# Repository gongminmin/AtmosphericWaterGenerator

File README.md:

# Atmospheric Water Generator

Atmospheric water generator (AWG) is a device for extracting fresh water from air. There are 0.0001% of water exists in the atmosphere. Even the desert air is not completely dry. Extract it for using is better than nothing. If the extraction is carried out near the ocean, where the air humidity is extremely high, the amount of fresh water obtained can be considerable. 

This is a simple open-source AWG design, suitable for home use. We'd like to make it easy to implement, so people can build it at home. The goals are:

* Low building cost. Off-shelve parts as much as possible.
* Easy to duplicate.
* Low operating cost and low power.
* Simple structure and easy maintenance.
* Small size and light weight.
* Safe and reliable.

## Principle

To extract water from air, we need a cold source. It condenses the water out for us to collect. The dry and cold air then be used to cool down the heat from the cold source device.

## Design

We use a [Peltier cooling plate](https://en.wikipedia.org/wiki/Thermoelectric_cooling) as the cold source. It's a solid semiconductor device, no moving part, easy to use. It as a cold side and a hot side. Two water cooling loops are circuiting between the surfaces of cooling plate to radiators. One loop carries the heat from a radiator to the cold side, makes the radiator cold. The other loop carries the heat from hot side to a radiator, exhaust the heat. The condensed water generated from the cold radiator drops down, collected by a bottle. The cooling plate is power consuming. We need a circuit to control it, keeping the temperature of the cold radiator in a certain range.

Most of the components are off-shelve ones. They are mounted to a frame by 3D printed adapters.

## Directories

* 3DModel folder is the 3D model design of some components. It's in STL format, ready for 3D printing.
* Circuit folder is the electric design of the system. The files can be open by [KiCad](https://kicad-pcb.org/)
* Code folder is the Arduino code for the control module.
* Doc folder contains some documents

## License

This project is distributed under the terms of MIT License. See [LICENSE](LICENSE) for details.

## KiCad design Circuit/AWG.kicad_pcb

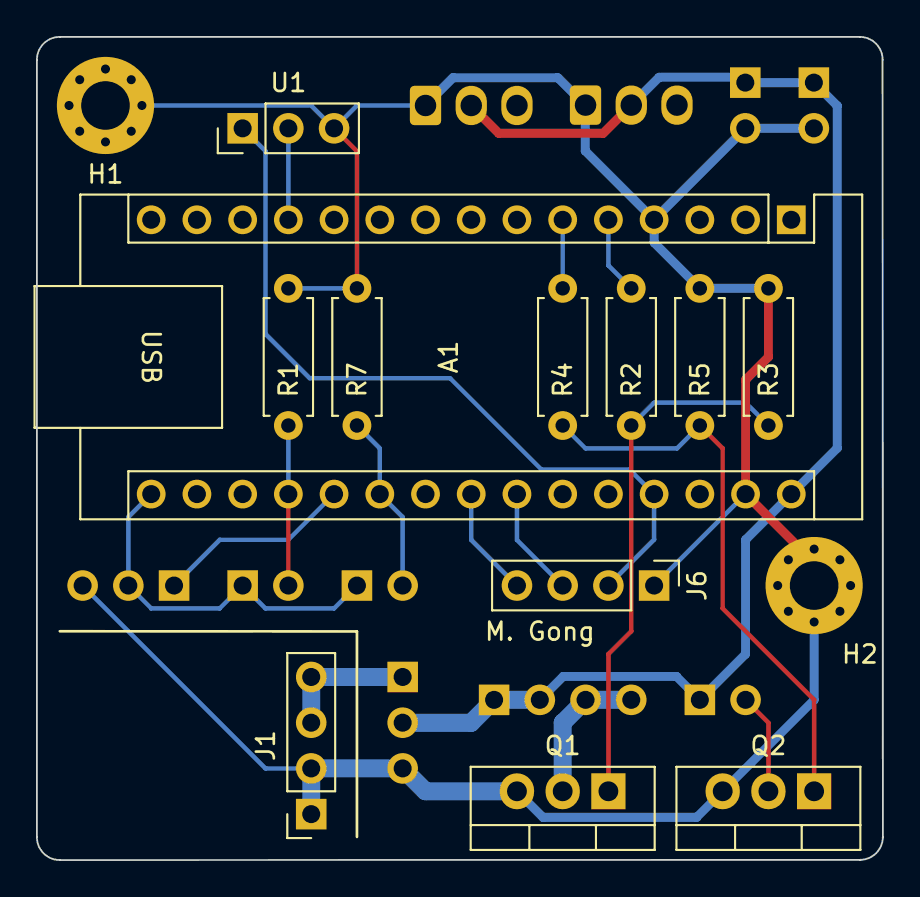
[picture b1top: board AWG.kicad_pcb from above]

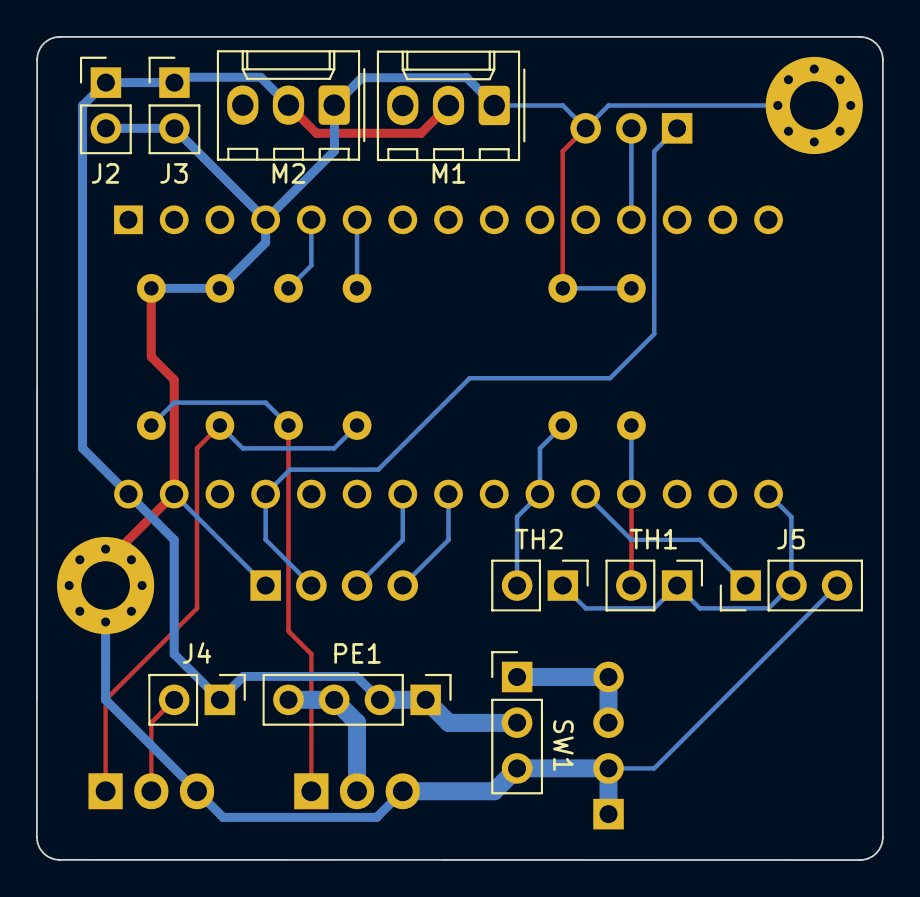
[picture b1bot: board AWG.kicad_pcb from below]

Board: 2 copper layers, 47.0 x 45.7 mm, 24 parts (10 on the bottom side), 17 nets.

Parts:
A1: Arduino_Nano_v3.x; Arduino_Nano
H1: H1; MountingHole_2.7mm_M2.5_Pad_Via
H2: H2; MountingHole_2.7mm_M2.5_Pad_Via
J1: Power; PinSocket_1x04_P2.54mm_Vertical
J2: Pump 1; PinHeader_1x02_P2.54mm_Vertical
J3: Pump 2; PinHeader_1x02_P2.54mm_Vertical
J4: Pump 3; PinHeader_1x02_P2.54mm_Vertical
J5: WL1; PinHeader_1x03_P2.54mm_Vertical
J6: Display; PinHeader_1x04_P2.54mm_Vertical
M1, M2: Fan_3pin; Molex_KK-254_AE-6410-03A_1x03_P2.54mm_Vertical
PE1: TEC1-12702; PinHeader_1x04_P2.54mm_Vertical
Q1, Q2: RFP30N06LE; TO-220-3_Vertical
R1, R3, R5, R7: 10K; R_Axial_DIN0207_L6.3mm_D2.5mm_P7.62mm_Horizontal
R2, R4: 100; R_Axial_DIN0207_L6.3mm_D2.5mm_P7.62mm_Horizontal
SW1: Switch; PinHeader_1x03_P2.54mm_Vertical
TH1, TH2: 10K; PinHeader_1x02_P2.54mm_Vertical
U1: DHT11; PinHeader_1x03_P2.54mm_Vertical

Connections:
+5V: A1.27 (+5V), J6.2, U1.1
+12V: A1.30 (VIN), J2.1, J3.1, J4.1, M1.2 (+), M2.2 (+), PE1.1, PE1.2, SW1.2
GND: A1.4 (GND), A1.29 (GND), H1.1, H2.1, J1.1, J1.2, J2.2, J3.2, J5.3, J6.1, M1.1 (-), M2.1 (-), Q1.3 (S), Q2.3 (S), R1.2, R3.2, R5.2, R7.2, SW1.3 (K), U1.3
unnamed: A1.19 (A0), R1.1, TH1.2
unnamed: A1.20 (A1), J5.1
unnamed: A1.21 (A2), R7.1, TH2.2
unnamed: A1.23 (A4), J6.4
unnamed: A1.24 (A5), J6.3
unnamed: A1.5 (D2), R2.1
unnamed: A1.6 (D3), R4.2
unnamed: A1.12 (D9), U1.2
unnamed: A1.16 (D13), J5.2, TH1.1, TH2.1
unnamed: J1.3, J1.4, SW1.1
unnamed: J4.2, Q2.2 (D)
unnamed: PE1.3, PE1.4, Q1.2 (D)
unnamed: Q1.1 (G), R2.2, R3.1
unnamed: Q2.1 (G), R4.1, R5.1

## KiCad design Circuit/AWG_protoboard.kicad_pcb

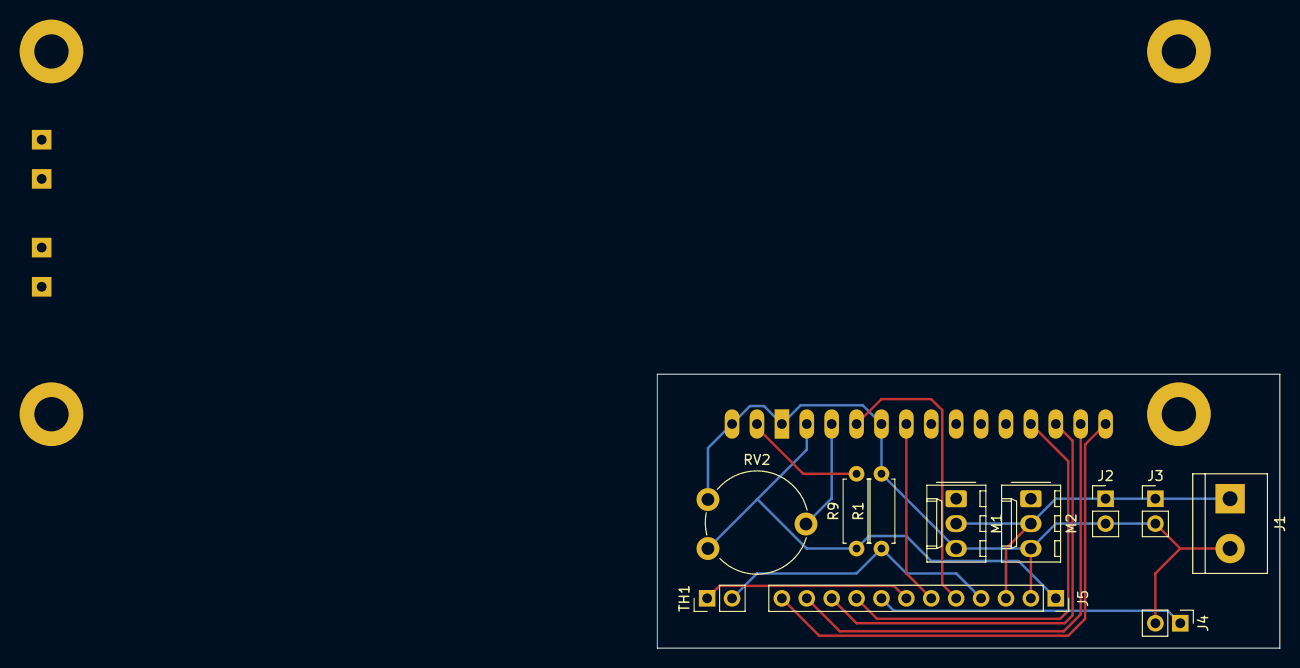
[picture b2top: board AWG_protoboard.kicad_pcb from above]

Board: 2 copper layers, 63.5 x 27.9 mm, 12 parts (1 on the bottom side), 14 nets.

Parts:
J1: Power; TerminalBlock_bornier-2_P5.08mm
J2: Pump 1; PinHeader_1x02_P2.54mm_Vertical
J3: Pump 2; PinHeader_1x02_P2.54mm_Vertical
J4: Mosfet; PinHeader_1x02_P2.54mm_Vertical
J5: Arduino; PinSocket_1x12_P2.54mm_Vertical
M1, M2: Fan_3pin; Molex_KK-254_AE-6410-03A_1x03_P2.54mm_Vertical
R1: 10K; R_Axial_DIN0207_L6.3mm_D2.5mm_P7.62mm_Horizontal
R9: 220; R_Axial_DIN0207_L6.3mm_D2.5mm_P7.62mm_Horizontal
RV2: R_Potentiometer; Potentiometer_Piher_PT-10-V10_Vertical
TH1: 10K; PinHeader_1x02_P2.54mm_Vertical
U2: LCD-016N002L

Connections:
+5V: J5.1, R9.1, RV2.1, U2.2 (VDD)
+12V: J1.1, J2.1, J3.1, J5.3, M1.2 (+), M2.2 (+)
/A0: J5.4, R1.1, TH1.2
/D2: J5.12, U2.14 (DB7)
/D3: J5.11, U2.13 (DB6)
/D4: J5.10, U2.12 (DB5)
/D5: J5.9, U2.11 (DB4)
/D6: J4.1, J5.8
/D7: J5.7, TH1.1
/D11: J5.6, U2.6 (E)
/D12: J5.5, U2.4 (RS)
GND: J1.2, J2.2, J3.2, J4.2, J5.2, M1.3 (-), M2.3 (-), R1.2, RV2.3, U2.1 (VSS), U2.5 (R/~W), U2.16 (K)
unnamed: R9.2, U2.15 (A/VEE)
unnamed: RV2.2, U2.3 (VO)

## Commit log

2023-03-25 Initial check in
2023-03-25 Add README
2023-03-25 Add 3D models of adapters
2023-03-25 Add circuit design
2023-03-25 Add document for prototype MK1
    Related issue: #1
2023-04-04 [Model] Add pipe spacer model, and update the water bottle cap model
2023-04-10 [Doc] Add document for prototype MK2
    Related issue: #2
2023-04-10 [Doc] Reduce the size of MK1 pictures
2023-04-10 [Doc] Fix typos and links in MK2 doc
2023-04-10 [Circuit] Change a resistor to a potentiometer to adjust upper bound of the switching
2023-04-27 [Doc] Update the MK2 doc
2023-04-27 [Code] Add test code for temperature measuring
    Related issue #6
2023-04-27 [Circuit] Redesign the control module, use an Arduino as the computation core
    Related issue #6
2023-05-01 [Circuit] Adjust the mosfet part in the circuit
2023-05-01 [Circuit] Import the footprint of heat sink
2023-05-02 [Circuit] Connect sensors to a digital output pin of the Arduino
2023-05-02 [Code] Add temperature range control code
    Related issue #6
2023-05-03 [Circuit] Fix the NTC symbol
2023-05-13 [3DModel] 3D printed upper and lower frames
    Related issue #5
2023-05-21 [Doc] Add document for prototype MK3
2024-02-05 [Circuit] Remove the unnecessary heatsinks
2024-02-06 [Circuit] Simplify the water level sensor to a connector
2024-02-10 [Circuit] Add protoboard design
2024-02-17 [Circuit] Improvements on protoboard layout
2024-02-28 [Circuit] Change to use I2C screen
2024-03-01 [Circuit] Switch to Arduino Nano
2024-03-04 [Code] Improve the text on display
    * Increase the font size.
    * Drop the loop frequency to 2Hz.
2024-03-04 [Circuit] Adjust footprints and references
2024-03-04 [Code] Add cooling plate status to display
2024-03-12 [Circuit][Code] Add a DHT module to measure environment temperature and humidity
2024-03-22 [3DModel] Update the cooling plate housing design
2024-03-23 [Circuit] Adjust the GPIOs and design a PCB
2025-08-30 [Circuit] Upgrade to KiCAD 9
2025-08-31 [Circuit] Fix symbol warnings
2026-02-06 [Circuit] Update the footprints
